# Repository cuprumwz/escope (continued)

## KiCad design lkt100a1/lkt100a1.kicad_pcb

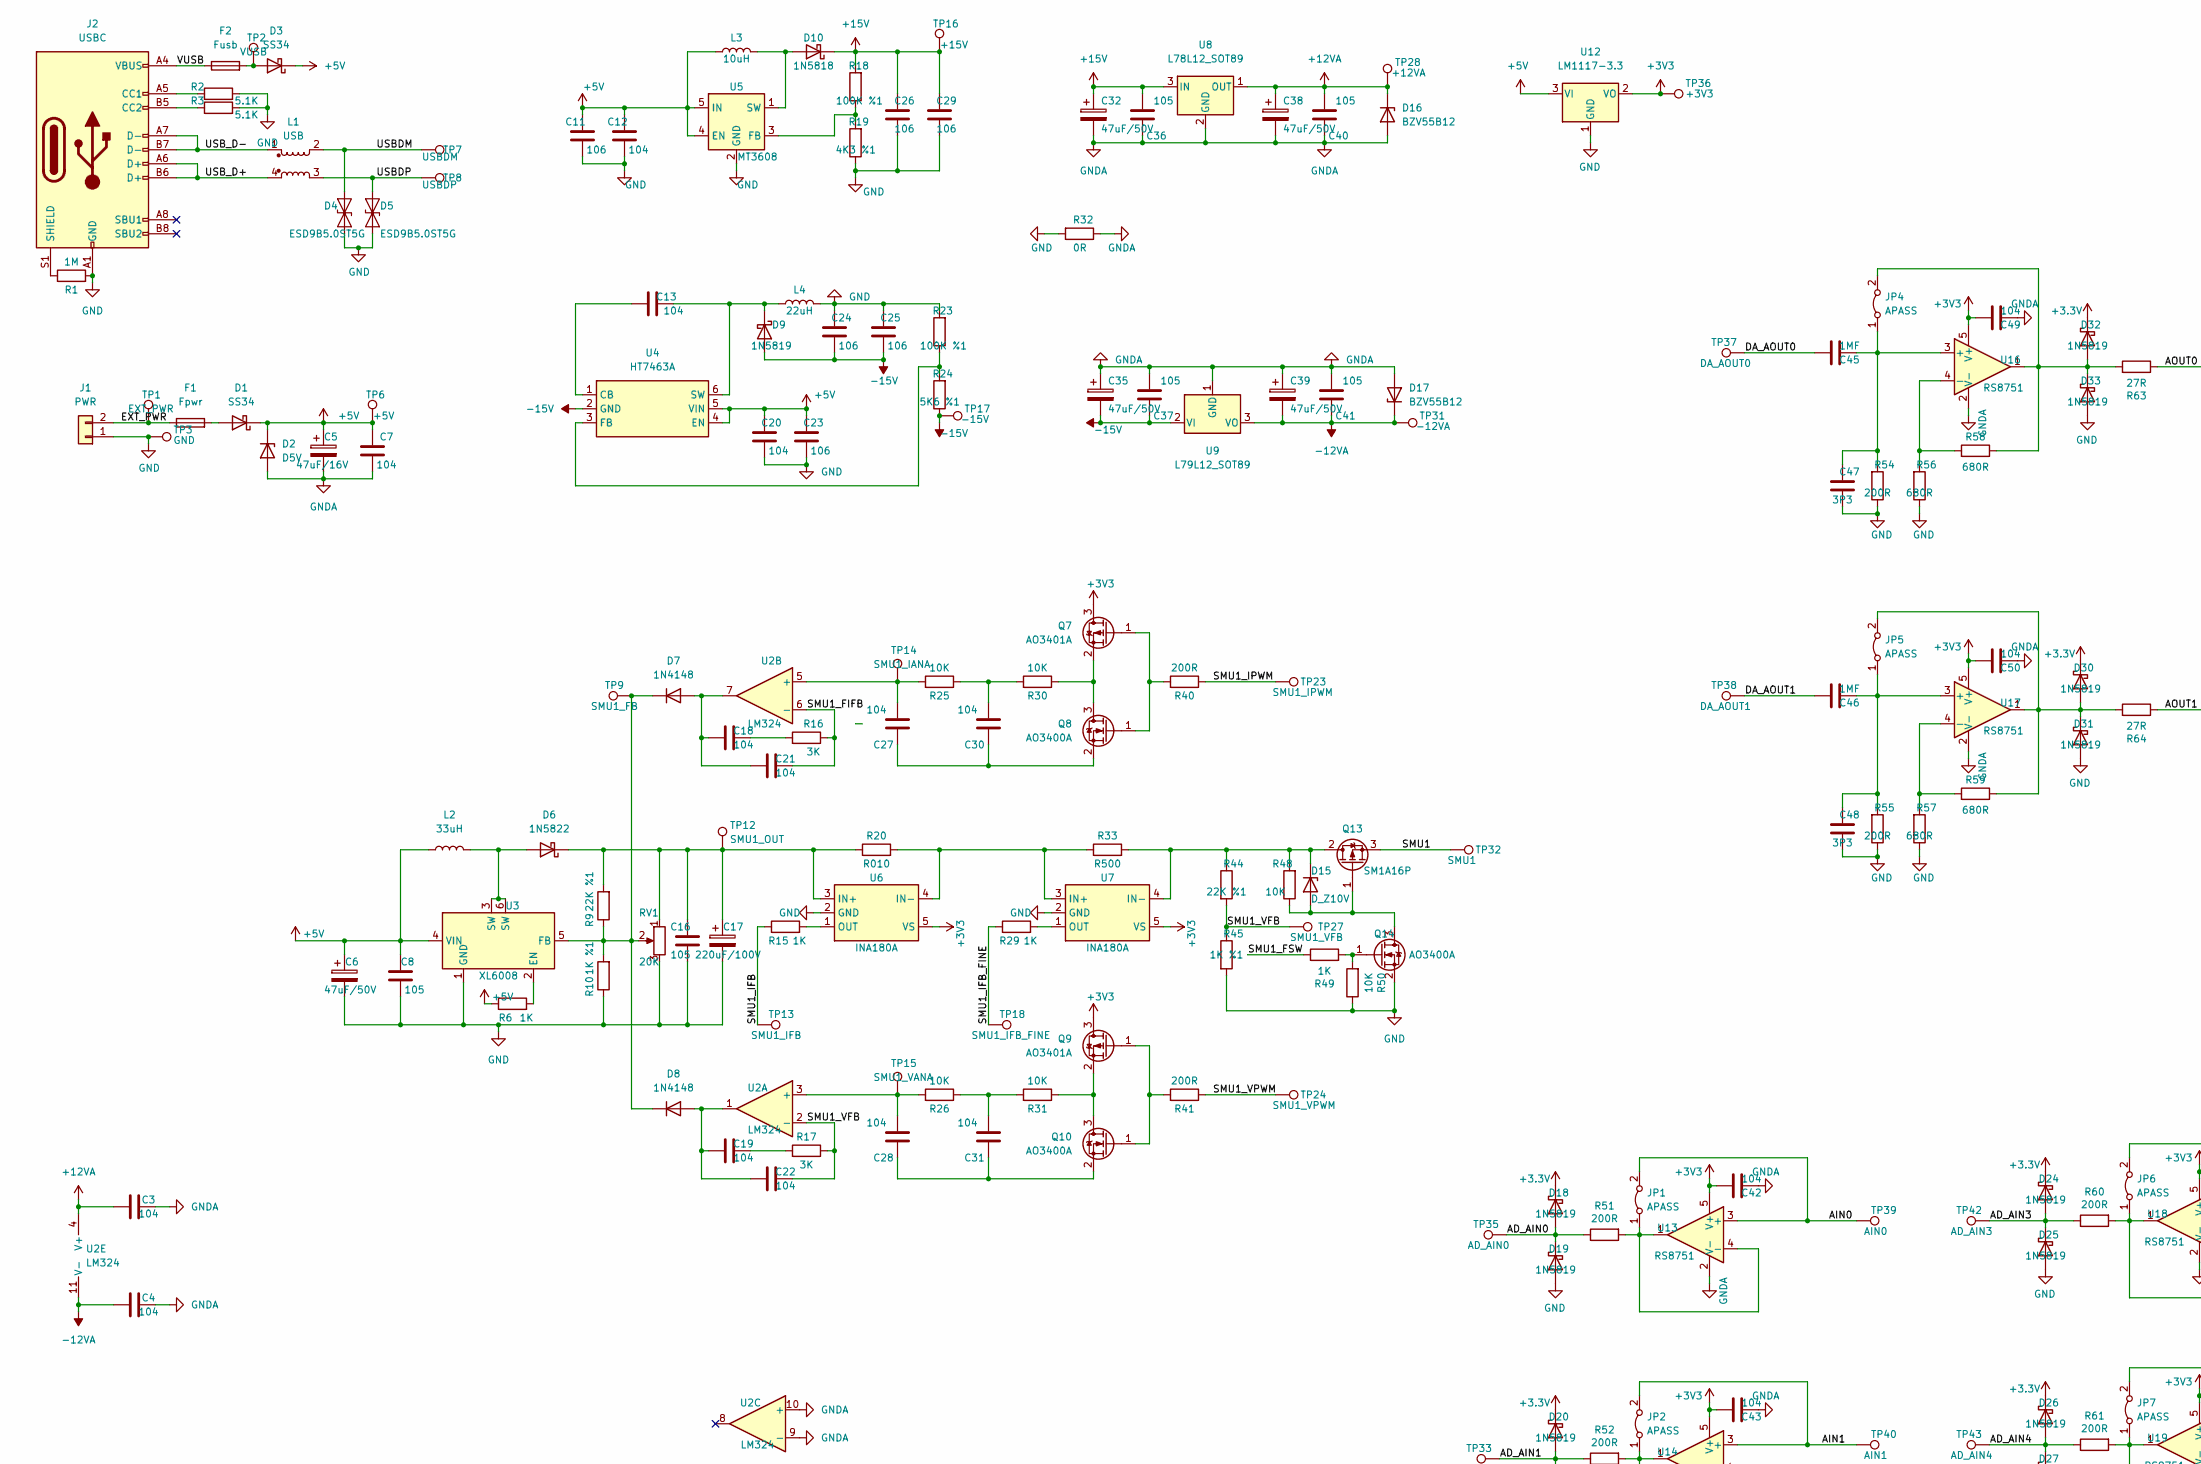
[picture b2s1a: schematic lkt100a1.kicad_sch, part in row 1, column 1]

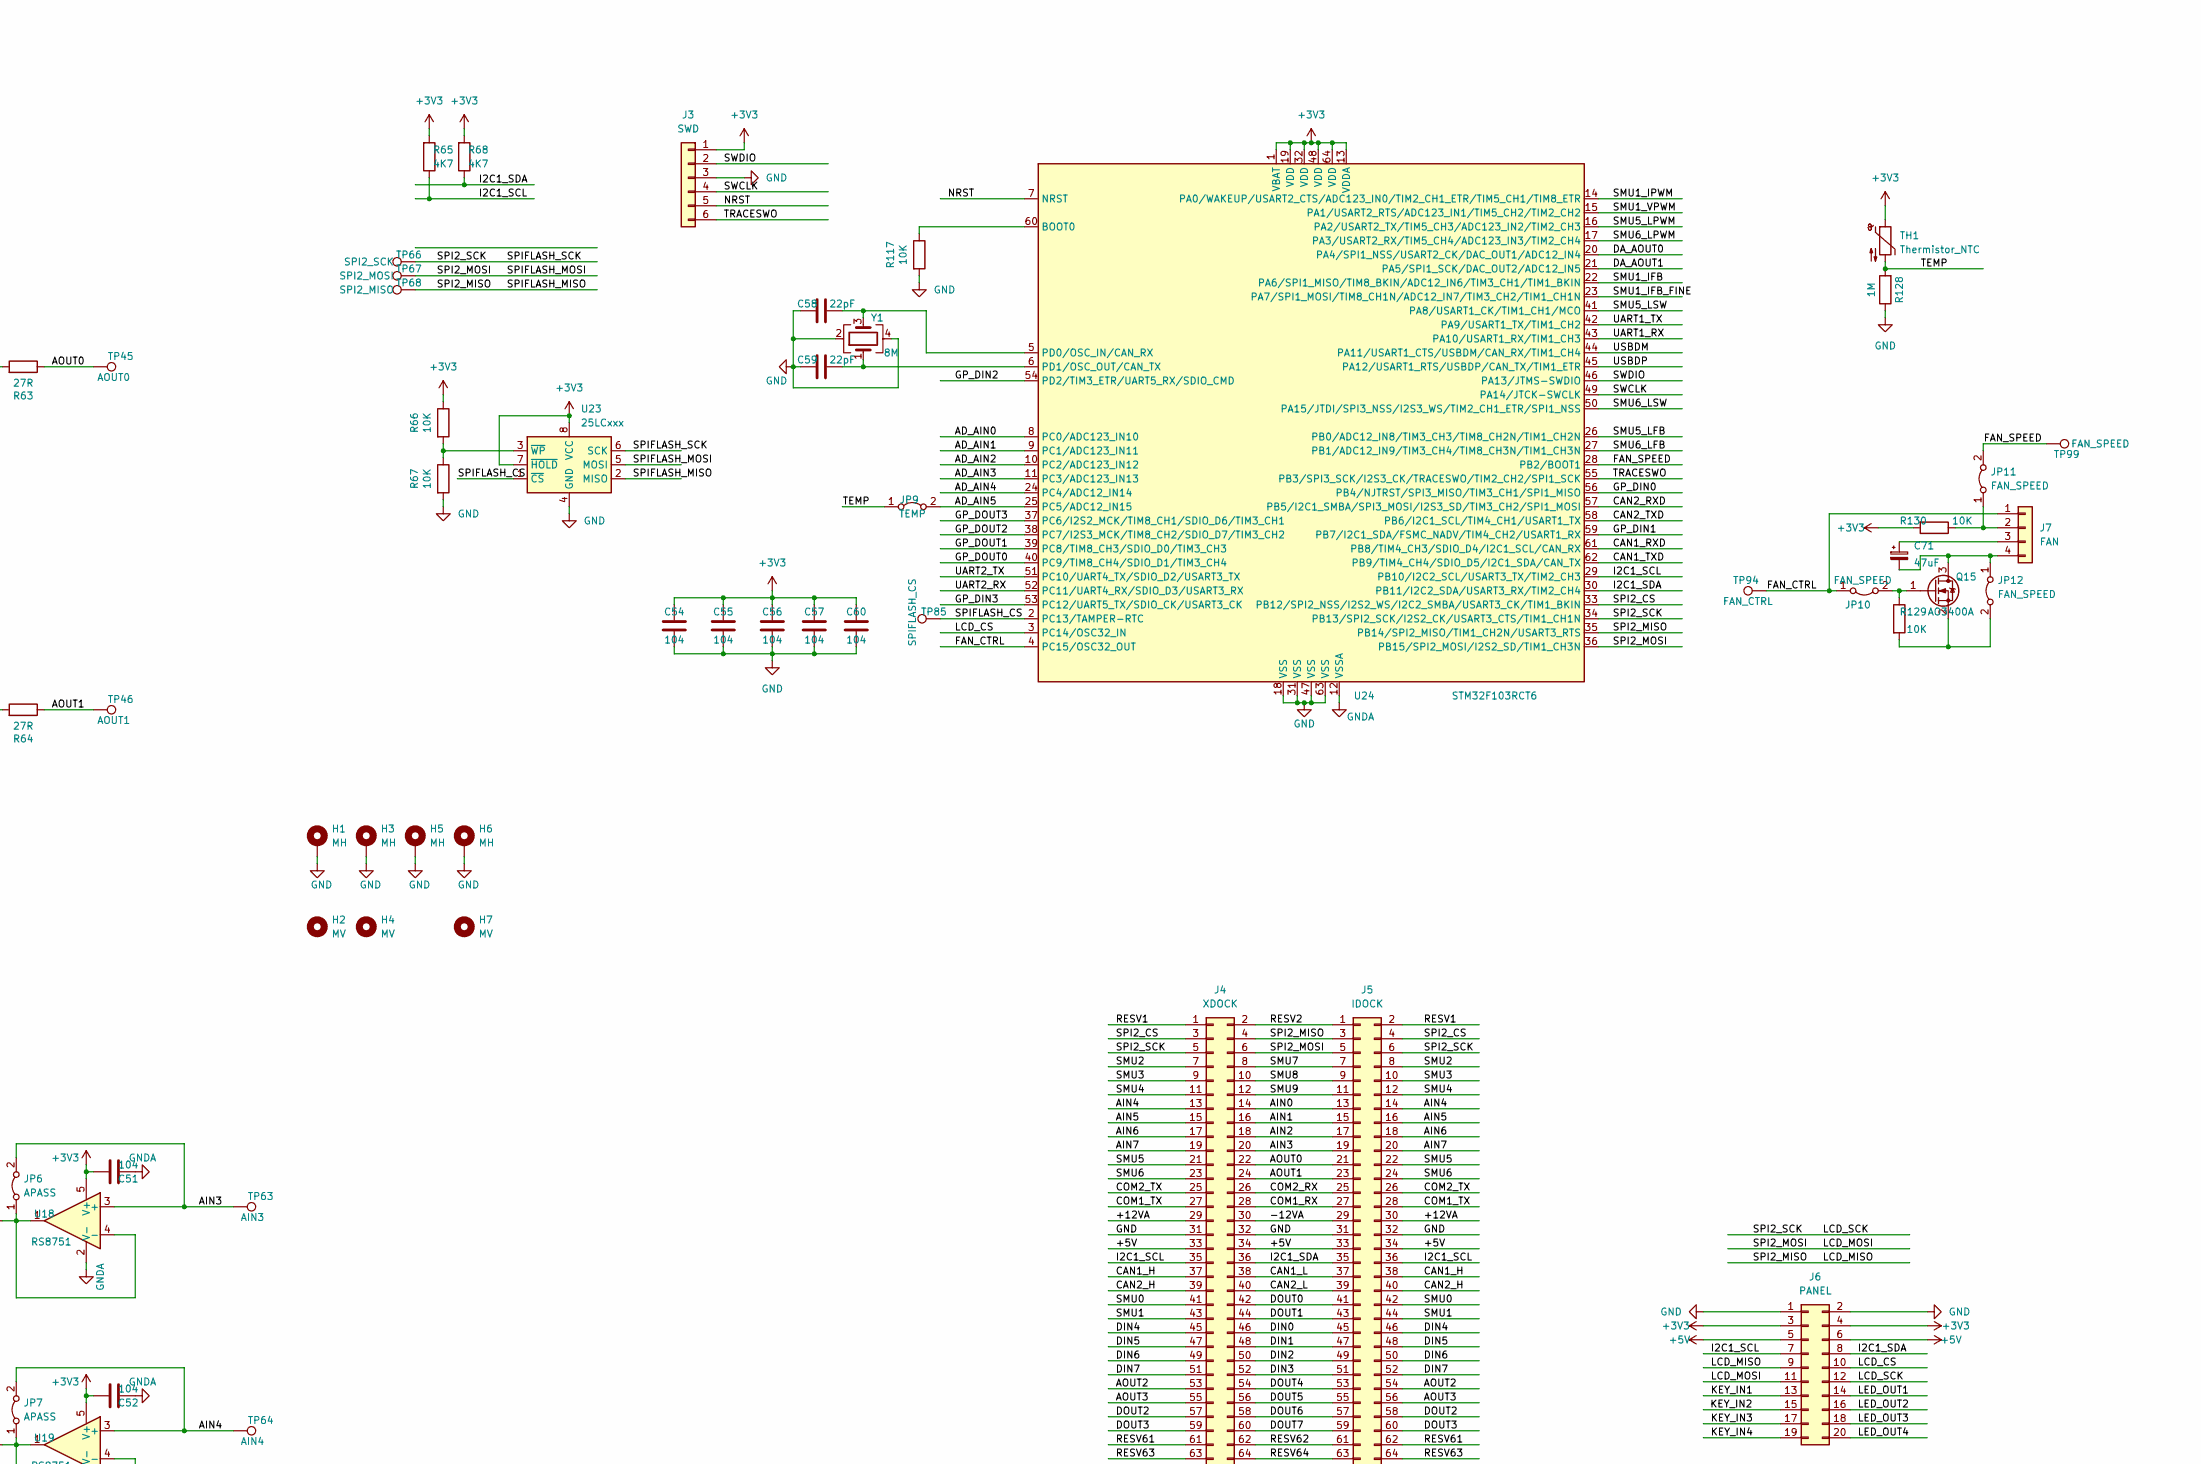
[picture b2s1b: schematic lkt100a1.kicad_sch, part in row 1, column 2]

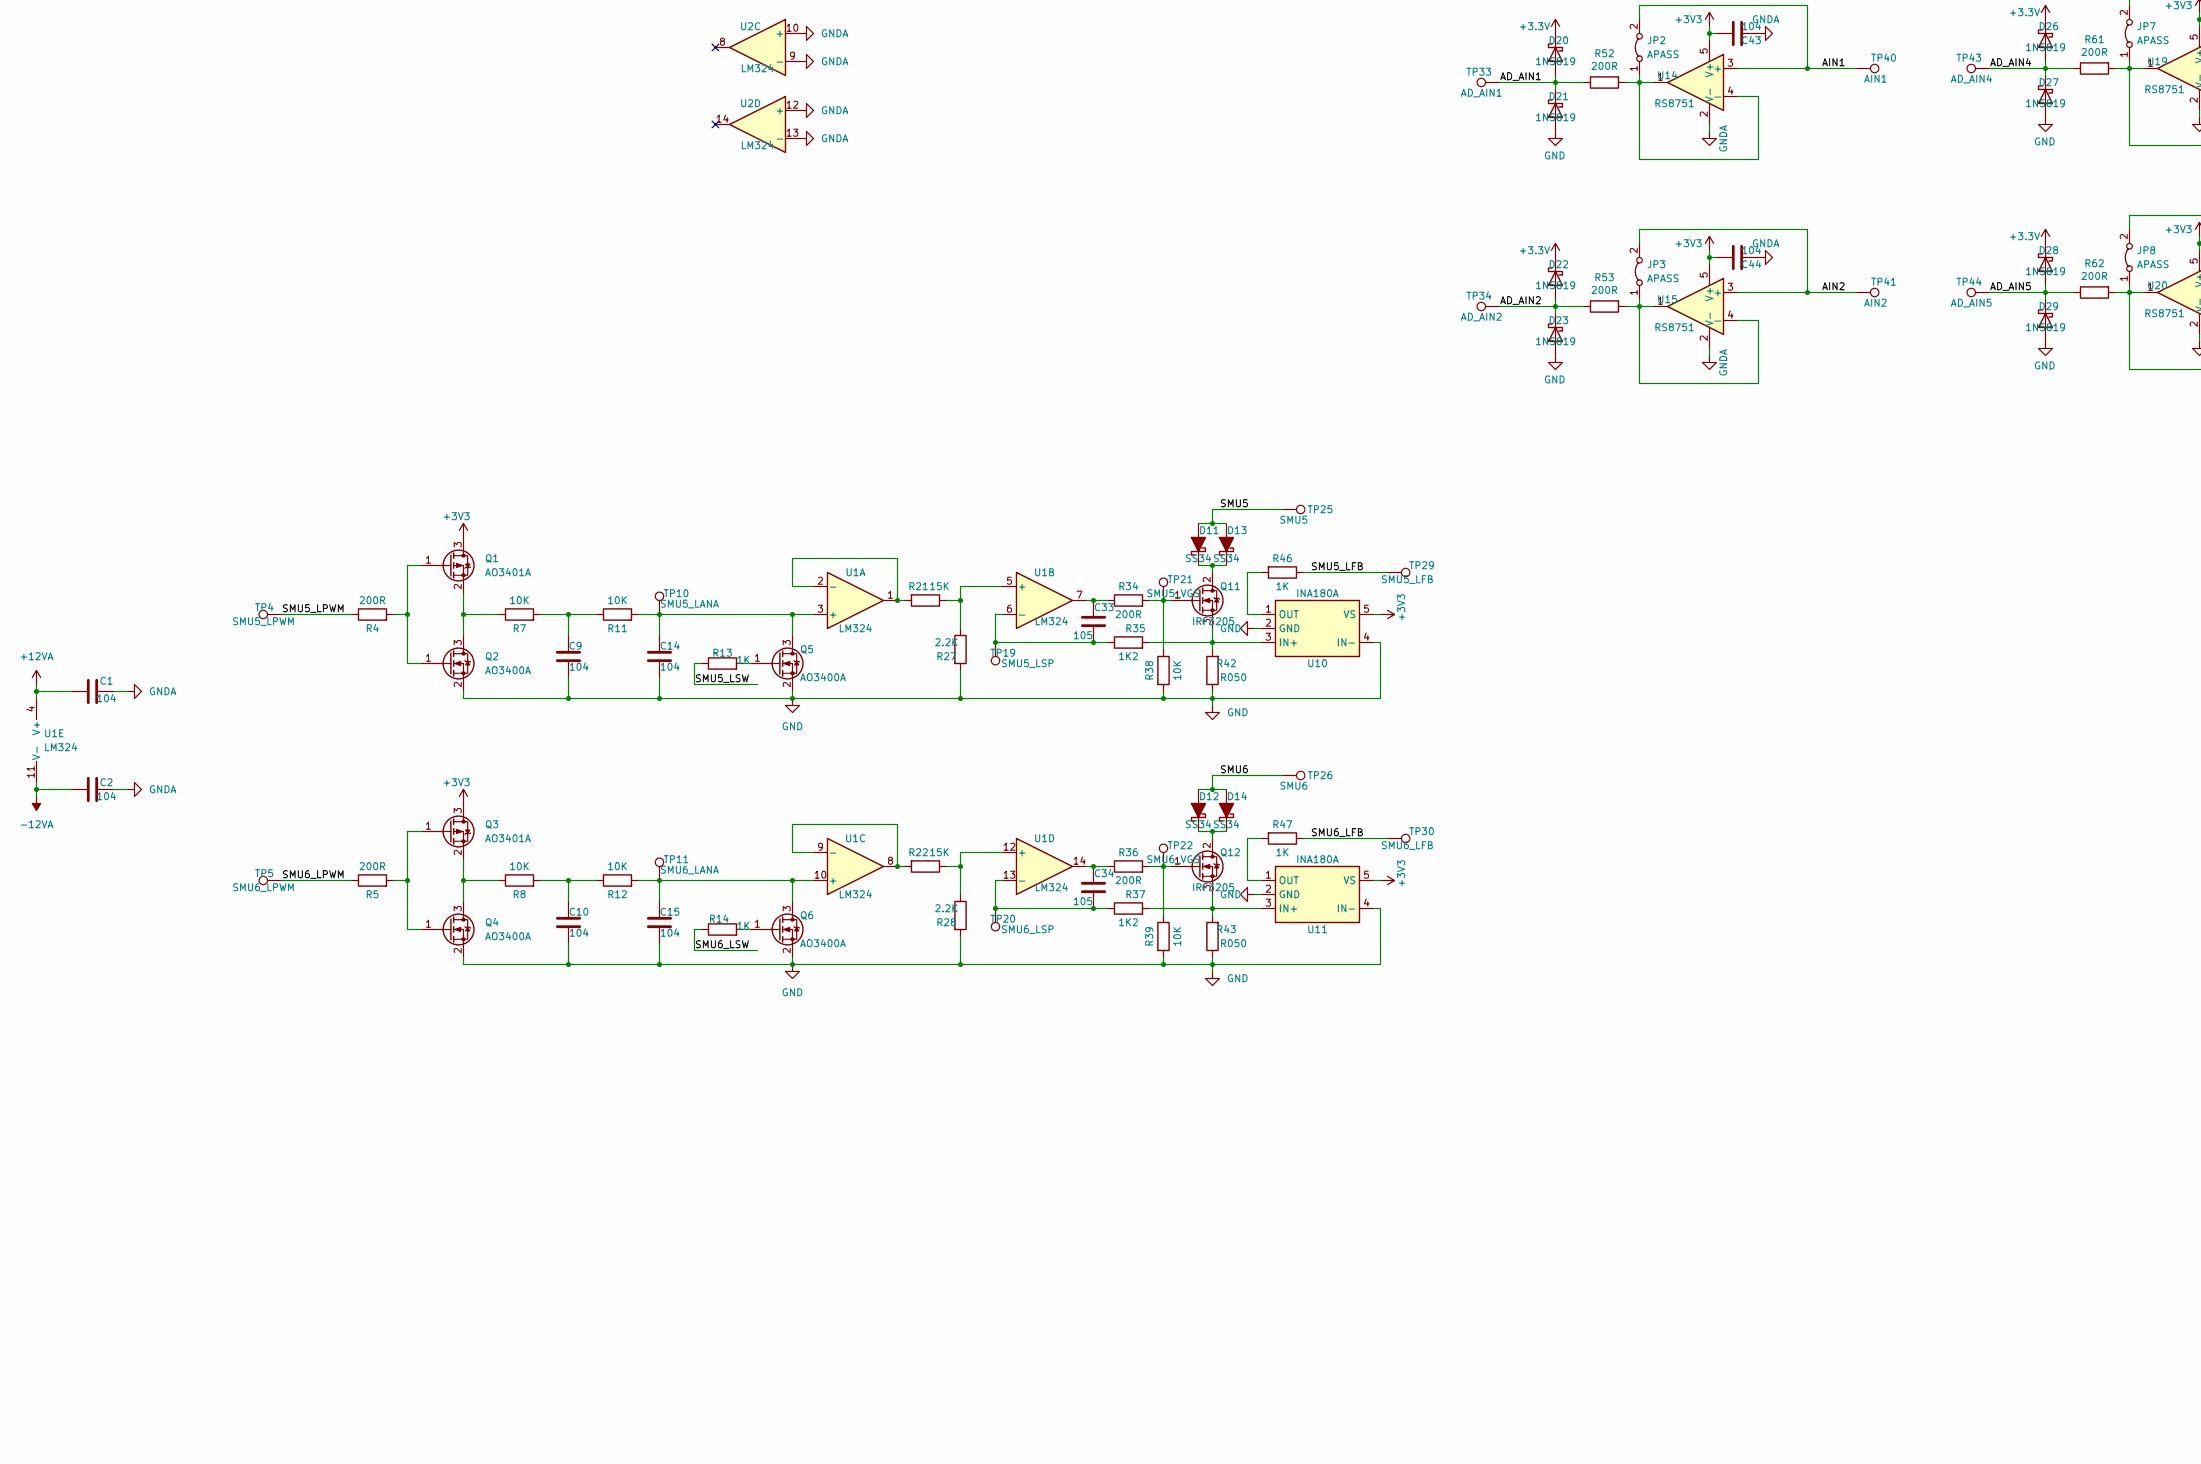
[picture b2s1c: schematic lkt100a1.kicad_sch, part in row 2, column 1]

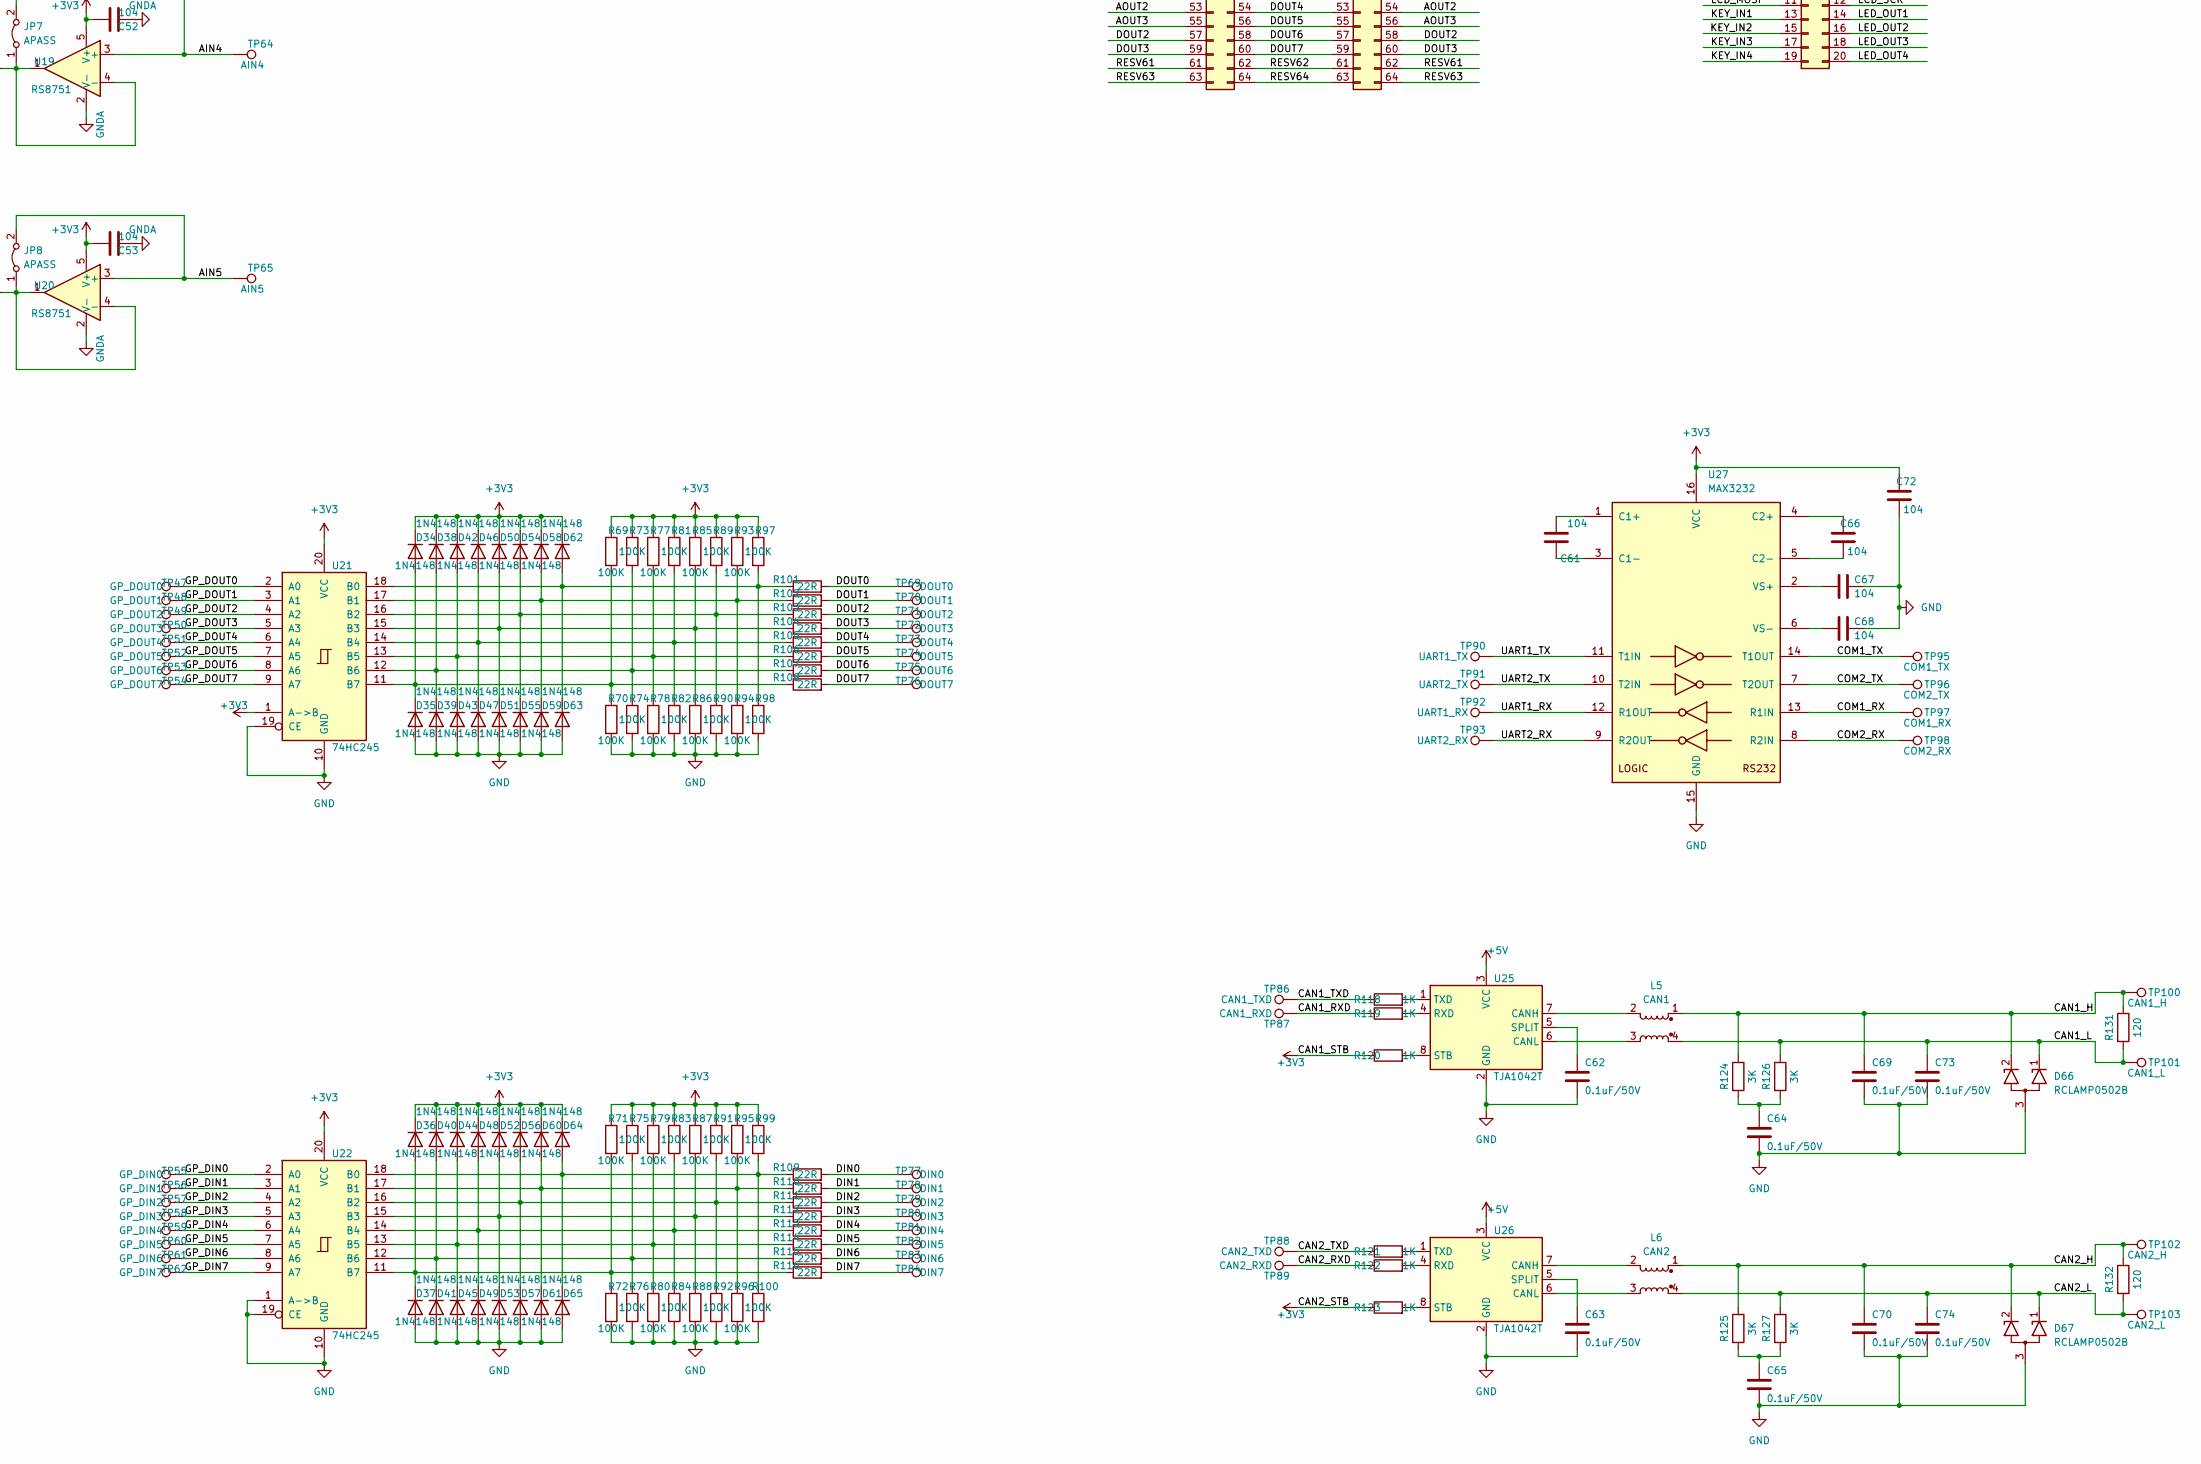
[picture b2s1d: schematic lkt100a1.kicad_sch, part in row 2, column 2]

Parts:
C1, C2, C3, C4, C7, C9, C10, C12, C13, C14, C15, C18, C19, C20, C21, C22, C27, C28, C30, C31, C42, C43, C44, C49, C50, C51, C52, C53, C54, C55, C56, C57, C60, C61, C66, C67, C68, C72: 104; C_0603_1608Metric
C5: 47uF/16V; CP_Elec_5x5.8
C6, C32, C35, C38, C39: 47uF/50V; CP_Elec_5x5.8
C8, C16, C33, C34, C36, C37, C40, C41: 105; C_0603_1608Metric
C11, C23, C24, C25, C26, C29: 106; C_0805_2012Metric
C17: 220uF/100V; CP_Elec_5x5.8
C45, C46: 1MF; C_0603_1608Metric
C47, C48: 3P3; C_0603_1608Metric
C58, C59: 22pF; C_0603_1608Metric
C62, C63, C64, C65, C69, C70, C73, C74: 0.1uF/50V; C_0603_1608Metric
C71: 47uF; CP_Elec_5x5.8
D1, D3, D11, D12, D13, D14: SS34; D_SMA-SMB_Universal_Handsoldering
D2: D5V; D_SMA-SMB_Universal_Handsoldering
D4, D5: ESD9B5.0ST5G; D_SOD-923
D6: 1N5822; D_SMA-SMB_Universal_Handsoldering
D7, D8, D34, D35, D36, D37, D38, D39, D40, D41, D42, D43, D44, D45, D46, D47, D48, D49, D50, D51, D52, D53, D54, D55, D56, D57, D58, D59, D60, D61, D62, D63, D64, D65: 1N4148; D_0805_2012Metric
D9: 1N5819; D_SMA-SMB_Universal_Handsoldering
D10: 1N5818; D_SMA-SMB_Universal_Handsoldering
D15: D_Z10V; D_SMA-SMB_Universal_Handsoldering
D16, D17: BZV55B12; D_MiniMELF
D18, D19, D20, D21, D22, D23, D24, D25, D26, D27, D28, D29, D30, D31, D32, D33: 1N5819; D_0805_2012Metric
D66, D67: RCLAMP0502B; SOT-416
F1: Fpwr; Fuse_2010_5025Metric
F2: Fusb; Fuse_1206_3216Metric
H1, H3, H5, H6: MH; MountingHole_2.7mm_M2.5_Pad_Via
H2, H4: MV; MountingHole_2.5mm
H7: MV; MountingHole_2.2mm_M2
J1: PWR; PinHeader_1x02_P2.54mm_Vertical
J2: USBC; USB_C_Receptacle_HRO_TYPE-C-31-M-12
J3: SWD; PinHeader_1x06_P2.00mm_Vertical
J4: XDOCK; IDC-Header_2x32_P2.54mm_Horizontal
J5: IDOCK; IDC-Header_2x32_P2.54mm_Vertical
J6: PANEL; IDC-Header_2x10_P2.54mm_Vertical
J7: FAN; JST_EH_B4B-EH-A_1x04_P2.50mm_Vertical
JP1, JP2, JP3, JP4, JP5, JP6, JP7, JP8: APASS; SolderJumper-2_P1.3mm_Open_TrianglePad1.0x1.5mm
JP9: TEMP; SolderJumper-2_P1.3mm_Open_TrianglePad1.0x1.5mm
JP10, JP11, JP12: FAN_SPEED; SolderJumper-2_P1.3mm_Open_TrianglePad1.0x1.5mm
L1: USB; L_CommonModeChoke_Coilcraft_0805USB
L2: 33uH; L_Toroid_Vertical_L13.0mm_W6.5mm_P5.60mm
L3: 10uH; L_Bourns-SRN6028
L4: 22uH; L_Bourns-SRN6028
L5: CAN1; L_CommonModeChoke_Coilcraft_1812CAN
L6: CAN2; L_CommonModeChoke_Coilcraft_1812CAN
Q1, Q3, Q7, Q9: AO3401A; SOT-23
Q2, Q4, Q5, Q6, Q8, Q10, Q14, Q15: AO3400A; SOT-23
Q11, Q12: IRF3205; TO-263-2
Q13: SM1A16P; TO-252-2
R1, R128: 1M; R_0603_1608Metric
R2, R3: 5.1K; R_0603_1608Metric
R4, R5, R34, R36, R40, R41, R51, R52, R53, R54, R55, R60, R61, R62: 200R; R_0603_1608Metric
R6, R13, R14, R15, R29, R46, R47, R49, R118, R119, R120, R121, R122, R123: 1K; R_0603_1608Metric
R7, R8, R11, R12, R25, R26, R30, R31, R38, R39, R50, R66, R67, R117, R129, R130: 10K; R_0603_1608Metric
R9, R44: 22K %1; R_0805_2012Metric
R10, R45: 1K %1; R_0805_2012Metric
R16, R17, R124, R125, R126, R127: 3K; R_0603_1608Metric
R18, R23: 100K %1; R_0805_2012Metric
R19: 4K3 %1; R_0805_2012Metric
R20: R010; R_1812_4532Metric
R21, R22: 15K; R_0603_1608Metric
R24: 5K6 %1; R_0805_2012Metric
R27, R28: 2.2K; R_0603_1608Metric
R32: 0R; R_0805_2012Metric
R33: R500; R_1812_4532Metric
R35, R37: 1K2; R_0603_1608Metric
R42, R43: R050; R_1812_4532Metric
R48: 10K; R_0805_2012Metric
R56, R57, R58, R59: 680R; R_0603_1608Metric
R63, R64: 27R; R_0603_1608Metric
R65, R68: 4K7; R_0603_1608Metric
R69, R70, R71, R72, R73, R74, R75, R76, R77, R78, R79, R80, R81, R82, R83, R84, R85, R86, R87, R88, R89, R90, R91, R92, R93, R94, R95, R96, R97, R98, R99, R100: 100K; R_0603_1608Metric
R101, R102, R103, R104, R105, R106, R107, R108, R109, R110, R111, R112, R113, R114, R115, R116: 22R; R_0603_1608Metric
R131, R132: 120; R_1206_3216Metric
RV1: 20K; Potentiometer_Bourns_3296W_Vertical
TH1: Thermistor_NTC; R_Axial_DIN0204_L3.6mm_D1.6mm_P2.54mm_Vertical
TP1: EXT_PWR; TestPoint_Pad_D1.0mm
TP2: VUSB; TestPoint_Pad_D1.0mm
TP3: GND; TestPoint_Pad_D1.0mm
TP4: SMU5_LPWM; TestPoint_Pad_D1.0mm
TP5: SMU6_LPWM; TestPoint_Pad_D1.0mm
TP6: +5V; TestPoint_Pad_D1.0mm
TP7: USBDM; TestPoint_Pad_D1.0mm
TP8: USBDP; TestPoint_Pad_D1.0mm
TP9: SMU1_FB; TestPoint_Pad_D1.0mm
TP10: SMU5_LANA; TestPoint_Pad_D1.0mm
TP11: SMU6_LANA; TestPoint_Pad_D1.0mm
TP12: SMU1_OUT; TestPoint_Pad_D1.0mm
TP13: SMU1_IFB; TestPoint_Pad_D1.0mm
TP14: SMU1_IANA; TestPoint_Pad_D1.0mm
TP15: SMU1_VANA; TestPoint_Pad_D1.0mm
TP16: +15V; TestPoint_Pad_D1.0mm
TP17: -15V; TestPoint_Pad_D1.0mm
TP18: SMU1_IFB_FINE; TestPoint_Pad_D1.0mm
TP19: SMU5_LSP; TestPoint_Pad_D1.0mm
TP20: SMU6_LSP; TestPoint_Pad_D1.0mm
TP21: SMU5_VGS; TestPoint_Pad_D1.0mm
TP22: SMU6_VGS; TestPoint_Pad_D1.0mm
TP23: SMU1_IPWM; TestPoint_Pad_D1.0mm
TP24: SMU1_VPWM; TestPoint_Pad_D1.0mm
TP25: SMU5; TestPoint_Pad_D1.0mm
TP26: SMU6; TestPoint_Pad_D1.0mm
TP27: SMU1_VFB; TestPoint_Pad_D1.0mm
TP28: +12VA; TestPoint_Pad_D1.0mm
TP29: SMU5_LFB; TestPoint_Pad_D1.0mm
TP30: SMU6_LFB; TestPoint_Pad_D1.0mm
TP31: -12VA; TestPoint_Pad_D1.0mm
TP32: SMU1; TestPoint_Pad_D1.0mm
TP33: AD_AIN1; TestPoint_Pad_D1.0mm
TP34: AD_AIN2; TestPoint_Pad_D1.0mm
TP35: AD_AIN0; TestPoint_Pad_D1.0mm
TP36: +3V3; TestPoint_Pad_D1.0mm
TP37: DA_AOUT0; TestPoint_Pad_D1.0mm
TP38: DA_AOUT1; TestPoint_Pad_D1.0mm
TP39: AIN0; TestPoint_Pad_D1.0mm
TP40: AIN1; TestPoint_Pad_D1.0mm
TP41: AIN2; TestPoint_Pad_D1.0mm
TP42: AD_AIN3; TestPoint_Pad_D1.0mm
TP43: AD_AIN4; TestPoint_Pad_D1.0mm
TP44: AD_AIN5; TestPoint_Pad_D1.0mm
TP45: AOUT0; TestPoint_Pad_D1.0mm
TP46: AOUT1; TestPoint_Pad_D1.0mm
TP47: GP_DOUT0; TestPoint_Pad_D1.0mm
TP48: GP_DOUT1; TestPoint_Pad_D1.0mm
TP49: GP_DOUT2; TestPoint_Pad_D1.0mm
TP50: GP_DOUT3; TestPoint_Pad_D1.0mm
TP51: GP_DOUT4; TestPoint_Pad_D1.0mm
TP52: GP_DOUT5; TestPoint_Pad_D1.0mm
TP53: GP_DOUT6; TestPoint_Pad_D1.0mm
TP54: GP_DOUT7; TestPoint_Pad_D1.0mm
TP55: GP_DIN0; TestPoint_Pad_D1.0mm
TP56: GP_DIN1; TestPoint_Pad_D1.0mm
TP57: GP_DIN2; TestPoint_Pad_D1.0mm
TP58: GP_DIN3; TestPoint_Pad_D1.0mm
TP59: GP_DIN4; TestPoint_Pad_D1.0mm
TP60: GP_DIN5; TestPoint_Pad_D1.0mm
TP61: GP_DIN6; TestPoint_Pad_D1.0mm
TP62: GP_DIN7; TestPoint_Pad_D1.0mm
TP63: AIN3; TestPoint_Pad_D1.0mm
TP64: AIN4; TestPoint_Pad_D1.0mm
TP65: AIN5; TestPoint_Pad_D1.0mm
TP66: SPI2_SCK; TestPoint_Pad_D1.0mm
TP67: SPI2_MOSI; TestPoint_Pad_D1.0mm
TP68: SPI2_MISO; TestPoint_Pad_D1.0mm
TP69: DOUT0; TestPoint_Pad_D1.0mm
TP70: DOUT1; TestPoint_Pad_D1.0mm
TP71: DOUT2; TestPoint_Pad_D1.0mm
TP72: DOUT3; TestPoint_Pad_D1.0mm
TP73: DOUT4; TestPoint_Pad_D1.0mm
TP74: DOUT5; TestPoint_Pad_D1.0mm
TP75: DOUT6; TestPoint_Pad_D1.0mm
TP76: DOUT7; TestPoint_Pad_D1.0mm
TP77: DIN0; TestPoint_Pad_D1.0mm
TP78: DIN1; TestPoint_Pad_D1.0mm
TP79: DIN2; TestPoint_Pad_D1.0mm
TP80: DIN3; TestPoint_Pad_D1.0mm
TP81: DIN4; TestPoint_Pad_D1.0mm
TP82: DIN5; TestPoint_Pad_D1.0mm
TP83: DIN6; TestPoint_Pad_D1.0mm
TP84: DIN7; TestPoint_Pad_D1.0mm
TP85: SPIFLASH_CS; TestPoint_Pad_D1.0mm
TP86: CAN1_TXD; TestPoint_Pad_D1.0mm
TP87: CAN1_RXD; TestPoint_Pad_D1.0mm
TP88: CAN2_TXD; TestPoint_Pad_D1.0mm
TP89: CAN2_RXD; TestPoint_Pad_D1.0mm
TP90: UART1_TX; TestPoint_Pad_D1.0mm
TP91: UART2_TX; TestPoint_Pad_D1.0mm
TP92: UART1_RX; TestPoint_Pad_D1.0mm
TP93: UART2_RX; TestPoint_Pad_D1.0mm
TP94: FAN_CTRL; TestPoint_Pad_D1.0mm
TP95: COM1_TX; TestPoint_Pad_D1.0mm
TP96: COM2_TX; TestPoint_Pad_D1.0mm
TP97: COM1_RX; TestPoint_Pad_D1.0mm
TP98: COM2_RX; TestPoint_Pad_D1.0mm
TP99: FAN_SPEED; TestPoint_Pad_D1.0mm
TP100: CAN1_H; TestPoint_Pad_D1.0mm
TP101: CAN1_L; TestPoint_Pad_D1.0mm
TP102: CAN2_H; TestPoint_Pad_D1.0mm
TP103: CAN2_L; TestPoint_Pad_D1.0mm
U1, U2: LM324; SO-14_3.9x8.65mm_P1.27mm
U3: XL6008; TO-252-5_TabPin6
U4: HT7463A; SOT-23-6
U5: MT3608; SOT-23-6
U6, U7, U10, U11: INA180A; SOT-23-5
U8: L78L12_SOT89; SOT-89-3
U9: L79L12_SOT89; SOT-89-3
U12: LM1117-3.3; SOT-223-3_TabPin2
U13, U14, U15, U16, U17, U18, U19, U20: RS8751; SOT-23-5
U21, U22: 74HC245; SOP-20_7.5x12.8mm_P1.27mm
U23: 25LCxxx; SOP-8_3.9x4.9mm_P1.27mm
U24: STM32F103RCT6; LQFP-64_10x10mm_P0.5mm
U25, U26: TJA1042T; SOIC-8_3.9x4.9mm_P1.27mm
U27: MAX3232; SOIC-16_4.55x10.3mm_P1.27mm
Y1: 8M; Crystal_SMD_3225-4Pin_3.2x2.5mm

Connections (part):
+5V: C5.1, C6.1, C7.2, C8.2, C11.2, C12.2, C20.2, C23.2, D1.1 (K), D2.1 (K), D3.1 (K), J4.33, J4.34, J5.33, J5.34, J6.5, J6.6, L2.1, L3.1, R6.1, TP6.1, U3.4 (VIN), U4.4 (EN), U4.5 (VIN), U5.4 (EN), U5.5 (IN), U12.3 (VI), U25.3 (VCC), U26.3 (VCC)
+12VA: C1.2, C3.2, C38.1, C40.2, D16.1 (K), J4.29, J5.30, TP28.1, U1.4 (V+), U2.4 (V+), U8.1 (OUT)
+15V: C26.2, C29.2, C32.1, C36.2, D10.1 (K), R18.2, TP16.1, U8.3 (IN)
-12VA: C2.2, C4.2, C39.2, C41.1, D17.1 (K), J4.30, J5.29, TP31.1, U1.11 (V-), U2.11 (V-), U9.3 (VO)
-15V: C24.1, C25.1, C35.2, C37.1, D9.2 (A), R24.1, TP17.1, U4.2 (GND), U9.2 (VI)
/AD_AIN0: D18.2 (A), D19.1 (K), R51.1, TP35.1, U24.8 (PC0/ADC123_IN10)
/AD_AIN1: D20.2 (A), D21.1 (K), R52.1, TP33.1, U24.9 (PC1/ADC123_IN11)
/AD_AIN2: D22.2 (A), D23.1 (K), R53.1, TP34.1, U24.10 (PC2/ADC123_IN12)
/AD_AIN3: D24.2 (A), D25.1 (K), R60.1, TP42.1, U24.11 (PC3/ADC123_IN13)
/AD_AIN4: D26.2 (A), D27.1 (K), R61.1, TP43.1, U24.24 (PC4/ADC12_IN14)
/AD_AIN5: D28.2 (A), D29.1 (K), JP9.2 (B), R62.1, TP44.1, U24.25 (PC5/ADC12_IN15)
/AIN0: J4.14, J5.13, JP1.2 (B), TP39.1, U13.3 (+)
/AIN1: J4.16, J5.15, JP2.2 (B), TP40.1, U14.3 (+)
/AIN2: J4.18, J5.17, JP3.2 (B), TP41.1, U15.3 (+)
/AIN3: J4.20, J5.19, JP6.2 (B), TP63.1, U18.3 (+)
/AIN4: J4.13, J5.14, JP7.2 (B), TP64.1, U19.3 (+)
/AIN5: J4.15, J5.16, JP8.2 (B), TP65.1, U20.3 (+)
/AIN6: J4.17, J5.18
/AIN7: J4.19, J5.20
/AOUT0: J4.22, J5.21, R63.1, TP45.1
/AOUT1: J4.24, J5.23, R64.1, TP46.1
/AOUT2: J4.53, J5.54
/AOUT3: J4.55, J5.56
/CAN1_H: C69.1, D66.2 (K2), J4.37, J5.38, L5.1, R124.1, R131.1, TP100.1
/CAN1_L: C73.1, D66.1 (K1), J4.38, J5.37, L5.4, R126.1, R131.2, TP101.1
/CAN1_RXD: R119.1, TP87.1, U24.61 (PB8/TIM4_CH3/SDIO_D4/I2C1_SCL/CAN_RX)
/CAN1_TXD: R118.1, TP86.1, U24.62 (PB9/TIM4_CH4/SDIO_D5/I2C1_SDA/CAN_TX)
/CAN2_H: C70.1, D67.2 (K2), J4.39, J5.40, L6.1, R125.1, R132.1, TP102.1
/CAN2_L: C74.1, D67.1 (K1), J4.40, J5.39, L6.4, R127.1, R132.2, TP103.1
/CAN2_RXD: R122.1, TP89.1, U24.57 (PB5/I2C1_SMBA/SPI3_MOSI/I2S3_SD/TIM3_CH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)
/CAN2_TXD: R121.1, TP88.1, U24.58 (PB6/I2C1_SCL/TIM4_CH1/USART1_TX)
/COM1_RX: J4.28, J5.27, TP97.1, U27.13 (R1IN)
/COM1_TX: J4.27, J5.28, TP95.1, U27.14 (T1OUT)
/COM2_RX: J4.26, J5.25, TP98.1, U27.8 (R2IN)
/COM2_TX: J4.25, J5.26, TP96.1, U27.7 (T2OUT)
/DA_AOUT0: C45.2, TP37.1, U24.20 (PA4/SPI1_NSS/USART2_CK/DAC_OUT1/ADC12_I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)
/DA_AOUT1: C46.2, TP38.1, U24.21 (PA5/SPI1_SCK/DAC_OUT2/ADC12_IN5)
/DIN0: J4.46, J5.45, R109.2, TP77.1
/DIN1: J4.48, J5.47, R110.2, TP78.1
/DIN2: J4.50, J5.49, R111.2, TP79.1
/DIN3: J4.52, J5.51, R112.2, TP80.1
/DIN4: J4.45, J5.46, R113.2, TP81.1
/DIN5: J4.47, J5.48, R114.2, TP82.1
/DIN6: J4.49, J5.50, R115.2, TP83.1
/DIN7: J4.51, J5.52, R116.2, TP84.1
/DOUT0: J4.42, J5.41, R101.2, TP69.1
/DOUT1: J4.44, J5.43, R102.2, TP70.1
/DOUT2: J4.57, J5.58, R103.2, TP71.1
/DOUT3: J4.59, J5.60, R104.2, TP72.1
/DOUT4: J4.54, J5.53, R105.2, TP73.1
/DOUT5: J4.56, J5.55, R106.2, TP74.1
/DOUT6: J4.58, J5.57, R107.2, TP75.1
/DOUT7: J4.60, J5.59, R108.2, TP76.1
/EXT_PWR: F1.1, J1.2, TP1.1
/FAN_CTRL: J7.1, JP10.1 (A), TP94.1, U24.4 (PC15/OSC32_OUT)
/FAN_SPEED: JP11.2 (B), TP99.1, U24.28 (PB2/BOOT1)
/GP_DIN0: TP55.1, U22.2 (A0), U24.56 (PB4/NJTRST/SPI3_MISO/TIM3_CH1/SPI1_MISO)
/GP_DIN1: TP56.1, U22.3 (A1), U24.59 (PB7/I2C1_SDA/FSMC_NADV/TIM4_CH2/USART1_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)
/GP_DIN2: TP57.1, U22.4 (A2), U24.54 (PD2/TIM3_ETR/UART5_RX/SDIO_CMD)
/GP_DIN3: TP58.1, U22.5 (A3), U24.53 (PC12/UART5_TX/SDIO_CK/USART3_CK)
/GP_DIN4: TP59.1, U22.6 (A4)
/GP_DIN5: TP60.1, U22.7 (A5)
/GP_DIN6: TP61.1, U22.8 (A6)
/GP_DIN7: TP62.1, U22.9 (A7)
/GP_DOUT0: TP47.1, U21.2 (A0), U24.40 (PC9/TIM8_CH4/SDIO_D1/TIM3_CH4)
/GP_DOUT1: TP48.1, U21.3 (A1), U24.39 (PC8/TIM8_CH3/SDIO_D0/TIM3_CH3)
/GP_DOUT2: TP49.1, U21.4 (A2), U24.38 (PC7/I2S3_MCK/TIM8_CH2/SDIO_D7/TIM3_CH2)
/GP_DOUT3: TP50.1, U21.5 (A3), U24.37 (PC6/I2S2_MCK/TIM8_CH1/SDIO_D6/TIM3_CH1)
/GP_DOUT4: TP51.1, U21.6 (A4)
/GP_DOUT5: TP52.1, U21.7 (A5)
/GP_DOUT6: TP53.1, U21.8 (A6)
/GP_DOUT7: TP54.1, U21.9 (A7)
/I2C1_SCL: J4.35, J5.36, J6.7, R65.1, U24.29 (PB10/I2C2_SCL/USART3_TX/TIM2_CH3)
/I2C1_SDA: J4.36, J5.35, J6.8, R68.1, U24.30 (PB11/I2C2_SDA/USART3_RX/TIM2_CH4)
/KEY_IN1: J6.13
/KEY_IN2: J6.15
/KEY_IN3: J6.17
/KEY_IN4: J6.19
/LCD_CS: J6.10, U24.3 (PC14/OSC32_IN)
/LCD_MISO: J4.4, J5.3, J6.9, TP68.1, U23.2 (MISO), U24.35 (PB14/SPI2_MISO/TIM1_CH2N/USART3_RTS)
/LCD_MOSI: J4.6, J5.5, J6.11, TP67.1, U23.5 (MOSI), U24.36 (PB15/SPI2_MOSI/I2S2_SD/TIM1_CH3N)
/LCD_SCK: J4.5, J5.6, J6.12, TP66.1, U23.6 (SCK), U24.34 (PB13/SPI2_SCK/I2S2_CK/USART3_CTS/TIM1_C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)
/LED_OUT1: J6.14
/LED_OUT2: J6.16
/LED_OUT3: J6.18
/LED_OUT4: J6.20
/NRST: J3.5, U24.7 (NRST)
/RESV1: J4.1, J5.2
/RESV2: J4.2, J5.1
/RESV61: J4.61, J5.62
/RESV62: J4.62, J5.61
/RESV63: J4.63, J5.64
/RESV64: J4.64, J5.63
/SMU0: J4.41, J5.42
/SMU1: J4.43, J5.44, Q13.3 (S), TP32.1
/SMU1_FIFB: C21.2, R16.1, U2.6 (-)
/SMU1_FSW: R49.1
/SMU1_IFB: R15.1, TP13.1, U24.22 (PA6/SPI1_MISO/TIM8_BKIN/ADC12_IN6/TIM3_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)
/SMU1_IFB_FINE: R29.1, TP18.1, U24.23 (PA7/SPI1_MOSI/TIM8_CH1N/ADC12_IN7/TIM3_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)
/SMU1_IPWM: R40.1, TP23.1, U24.14 (PA0/WAKEUP/USART2_CTS/ADC123_IN0/TIM2_C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)
/SMU1_VFB: C22.2, R17.1, R44.2, R45.1, TP27.1, U2.2 (-)
/SMU1_VPWM: R41.1, TP24.1, U24.15 (PA1/USART2_RTS/ADC123_IN1/TIM5_CH2/TIM2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)
/SMU2: J4.7, J5.8
/SMU3: J4.9, J5.10
/SMU4: J4.11, J5.12
/SMU5: D11.2 (A), D13.2 (A), J4.21, J5.22, TP25.1
/SMU5_LFB: R46.1, TP29.1, U24.26 (PB0/ADC12_IN8/TIM3_CH3/TIM8_CH2N/TIM1_C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)
/SMU5_LPWM: R4.1, TP4.1, U24.16 (PA2/USART2_TX/TIM5_CH3/ADC123_IN2/TIM2_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)
/SMU5_LSW: R13.1, U24.41 (PA8/USART1_CK/TIM1_CH1/MCO)
/SMU6: D12.2 (A), D14.2 (A), J4.23, J5.24, TP26.1
/SMU6_LFB: R47.1, TP30.1, U24.27 (PB1/ADC12_IN9/TIM3_CH4/TIM8_CH3N/TIM1_C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)
/SMU6_LPWM: R5.1, TP5.1, U24.17 (PA3/USART2_RX/TIM5_CH4/ADC123_IN3/TIM2_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)
/SMU6_LSW: R14.1, U24.50 (PA15/JTDI/SPI3_NSS/I2S3_WS/TIM2_CH1_ETR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)
/SMU7: J4.8, J5.7
/SMU8: J4.10, J5.9
/SMU9: J4.12, J5.11
/SPI2_CS: J4.3, J5.4, U24.33 (PB12/SPI2_NSS/I2S2_WS/I2C2_SMBA/USART3_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)
/SPIFLASH_CS: TP85.1, U23.1 (~CS), U24.2 (PC13/TAMPER-RTC)
/SWCLK: J3.4, U24.49 (PA14/JTCK-SWCLK)
/SWDIO: J3.2, U24.46 (PA13/JTMS-SWDIO)
/TEMP: JP9.1 (A), R128.2, TH1.2
/TRACESWO: J3.6, U24.55 (PB3/SPI3_SCK/I2S3_CK/TRACESWO/TIM2_CH2/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)
/UART1_RX: TP92.1, U24.43 (PA10/USART1_RX/TIM1_CH3), U27.12 (R1OUT)
/UART1_TX: TP90.1, U24.42 (PA9/USART1_TX/TIM1_CH2), U27.11 (T1IN)
/UART2_RX: TP93.1, U24.52 (PC11/UART4_RX/SDIO_D3/USART3_RX), U27.9 (R2OUT)
/UART2_TX: TP91.1, U24.51 (PC10/UART4_TX/SDIO_D2/USART3_TX), U27.10 (T2IN)
/USBDM: D4.1 (A1), L1.2, TP7.1, U24.44 (PA11/USART1_CTS/USBDM/CAN_RX/TIM1_CH4)
/USBDP: D5.1 (A1), L1.3, TP8.1, U24.45 (PA12/USART1_RTS/USBDP/CAN_TX/TIM1_ETR)
/USB_D+: J2.A6 (D+), J2.B6 (D+), L1.4
/USB_D-: J2.A7 (D-), J2.B7 (D-), L1.1
/VUSB: F2.1, J2.A4 (VBUS), J2.A9 (VBUS), J2.B4 (VBUS), J2.B9 (VBUS)
GND: C6.2, C8.1, C9.1, C10.1, C11.1, C12.1, C14.1, C15.1, C16.1, C17.2, C20.1, C23.1, C24.2, C25.2, C26.1, C29.1, C47.2, C48.2, C54.1, C55.1, C56.1, C57.1, C58.1, C59.1, C60.1, C62.2, C63.2, C64.2, C65.2, C67.2, C68.2, C69.2, C70.2, C72.2, C73.2, C74.2, D4.2 (A2), D5.2 (A2), D19.2 (A), D21.2 (A), D23.2 (A), D25.2 (A), D27.2 (A), D29.2 (A), D31.2 (A), D33.2 (A), D35.2 (A), D37.2 (A), D39.2 (A), D41.2 (A), D43.2 (A), D45.2 (A), D47.2 (A), D49.2 (A), D51.2 (A), D53.2 (A), D55.2 (A), D57.2 (A), D59.2 (A), D61.2 (A), D63.2 (A), D65.2 (A), D66.3 (A), D67.3 (A), H1.1, H3.1, H5.1, H6.1, J1.1, J2.A1 (GND), J2.A12 (GND), J2.B1 (GND), J2.B12 (GND), J3.3, J4.31, J4.32, J5.31, J5.32, J6.1, J6.2, L4.2, Q2.2 (S), Q4.2 (S), Q5.2 (S)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
GNDA: C1.1, C2.1, C3.1, C4.1, C5.2, C7.1, C32.2, C35.1, C36.1, C37.2, C38.2, C39.1, C40.1, C41.2, C42.1, C43.1, C44.1, C49.1, C50.1, C51.1, C52.1, C53.1, D2.2 (A), D16.2 (A), D17.2 (A), R32.1, U2.9 (-), U2.10 (+), U2.12 (+), U2.13 (-), U8.2 (GND), U9.1 (GND), U13.2 (V-), U14.2 (V-), U15.2 (V-), U16.2 (V-), U17.2 (V-), U18.2 (V-), U19.2 (V-), U20.2 (V-), U24.12 (VSSA)
unnamed: C9.2, R7.2, R11.1
unnamed: C10.2, R8.2, R12.1
unnamed: C13.1, D9.1 (K), L4.1, U4.6 (SW)
unnamed: C13.2, U4.1 (CB)
unnamed: C14.2, Q5.3 (D), R11.2, TP10.1, U1.3 (+)
unnamed: C15.2, Q6.3 (D), R12.2, TP11.1, U1.10 (+)
unnamed: C16.2, C17.1, D6.1 (K), R9.2, R20.1, RV1.1, TP12.1, U6.3 (IN+)
unnamed: C18.1, C21.1, D7.2 (A), U2.7
unnamed: C18.2, R16.2
unnamed: C19.1, C22.1, D8.2 (A), U2.1
unnamed: C19.2, R17.2
unnamed: C27.1, C30.1, Q8.2 (S)
unnamed: C27.2, R25.2, TP14.1, U2.5 (+)
unnamed: C28.1, C31.1, Q10.2 (S)
unnamed: C28.2, R26.2, TP15.1, U2.3 (+)
unnamed: C30.2, R25.1, R30.2
unnamed: C31.2, R26.1, R31.2
unnamed: C33.1, R34.1, U1.7
unnamed: C33.2, R35.1, TP19.1, U1.6 (-)
unnamed: C34.1, R36.1, U1.14
unnamed: C34.2, R37.1, TP20.1, U1.13 (-)
unnamed: C45.1, C47.1, JP4.1 (A), R54.2, U16.3 (+)
unnamed: C46.1, C48.1, JP5.1 (A), R55.2, U17.3 (+)
unnamed: C58.2, U24.5 (PD0/OSC_IN/CAN_RX), Y1.3
unnamed: C59.2, U24.6 (PD1/OSC_OUT/CAN_TX), Y1.1
unnamed: C61.1, U27.3 (C1-)
unnamed: C61.2, U27.1 (C1+)
unnamed: C62.1, U25.5 (SPLIT)
unnamed: C63.1, U26.5 (SPLIT)
unnamed: C64.1, R124.2, R126.2
unnamed: C65.1, R125.2, R127.2
unnamed: C66.1, U27.4 (C2+)
unnamed: C66.2, U27.5 (C2-)
unnamed: C67.1, U27.2 (VS+)
unnamed: C68.1, U27.6 (VS-)
unnamed: C71.1, J7.3
unnamed: C71.2, J7.4, JP12.1 (A), Q15.3 (D)
unnamed: D1.2 (A), F1.2
unnamed: D3.2 (A), F2.2, TP2.1
unnamed: D6.2 (A), L2.2, U3.3 (SW), U3.6 (SW)
unnamed: D7.1 (K), D8.1 (K), R9.1, R10.2, RV1.2, TP9.1, U3.5 (FB)
unnamed: D10.2 (A), L3.2, U5.1 (SW)
unnamed: D11.1 (K), D13.1 (K), Q11.2 (D)
unnamed: D12.1 (K), D14.1 (K), Q12.2 (D)
unnamed: D15.1 (K), Q13.2 (D), R33.2, R44.1, R48.2, U7.4 (IN-)
unnamed: D15.2 (A), Q13.1 (G), Q14.3 (D), R48.1
unnamed: D30.2 (A), D31.1 (K), JP5.2 (B), R59.1, R64.2, U17.1
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
